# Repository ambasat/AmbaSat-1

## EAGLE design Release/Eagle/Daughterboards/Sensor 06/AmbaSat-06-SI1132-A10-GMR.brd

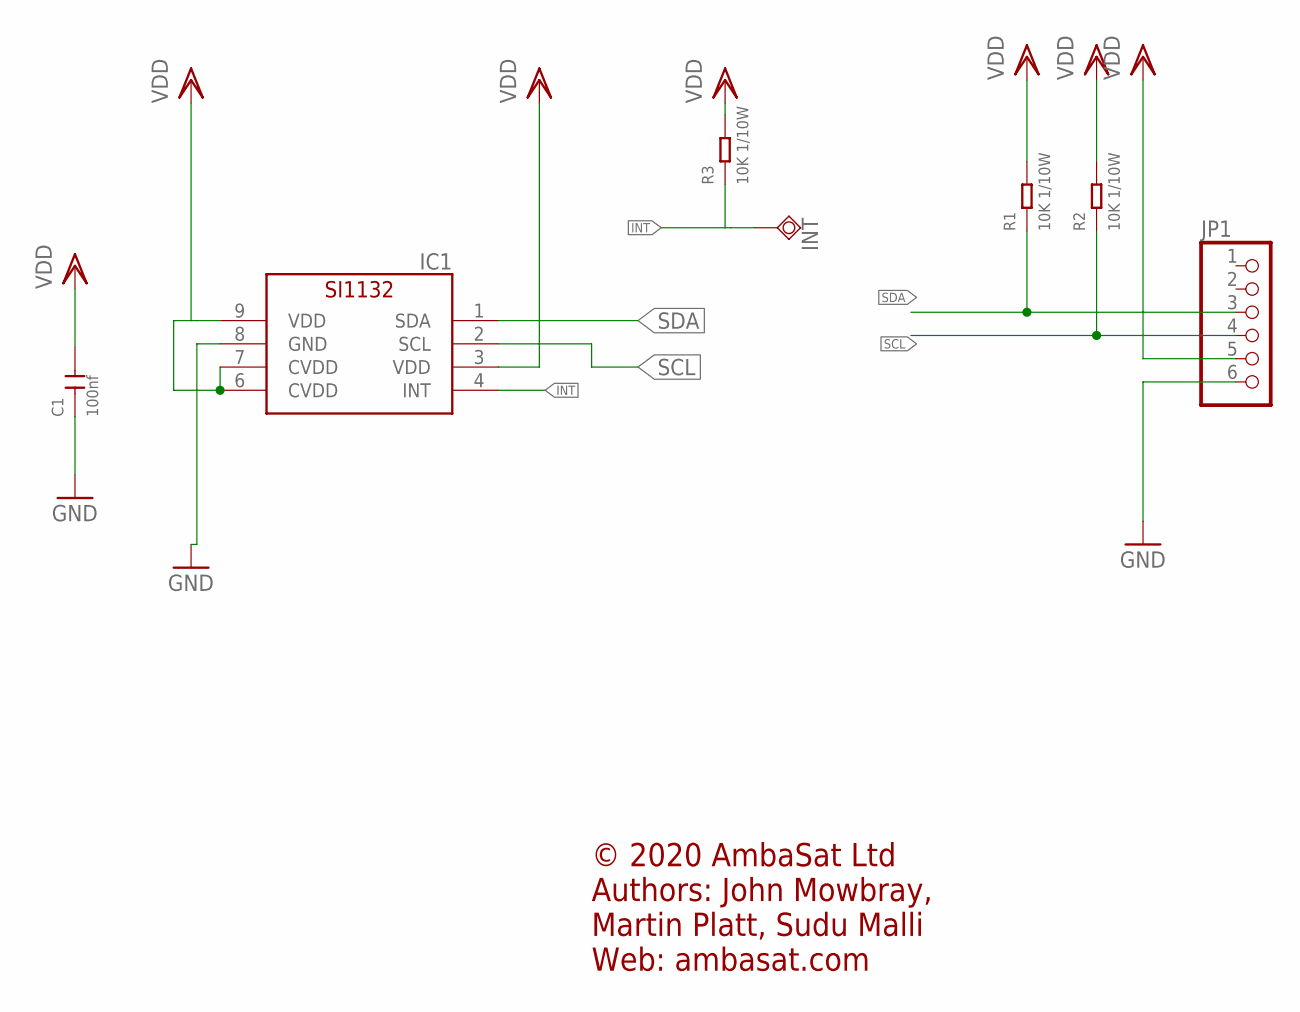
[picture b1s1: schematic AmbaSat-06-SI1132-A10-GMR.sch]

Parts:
C1: 100nf; C0603
IC1: SL-SI1132; SILICONLABS-SI1132
INT: TESTPAD_TPSQTP12R; TESTPAD_TP12R
JP1: HEADER-1X6; 1X06_OVAL
R1, R2, R3: 10K 1/10W; R0603

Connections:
GND: C1.1, IC1.8 (GND), JP1.6
INT: IC1.4 (INT), INT.TP, R3.1
SCL: IC1.2 (SCL), JP1.4, R2.1
SDA: IC1.1 (SDA), JP1.3, R1.1
VDD: C1.2, IC1.3 (VDD), IC1.6 (CVDD), IC1.7 (CVDD), IC1.9 (VDD), JP1.5, R1.2, R2.2, R3.2

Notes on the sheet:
© 2020 AmbaSat Ltd Authors: John Mowbray, Martin Platt, Sudu Malli Web: ambasat.com

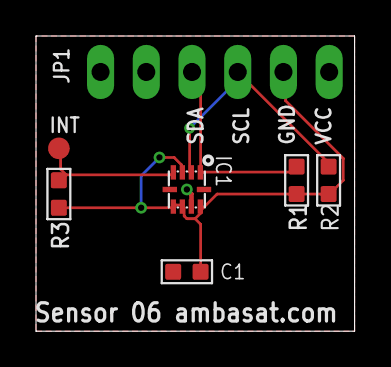
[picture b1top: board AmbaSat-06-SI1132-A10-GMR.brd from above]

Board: 2 copper layers, 17.7 x 16.4 mm, 7 parts (0 on the bottom side), 5 nets.

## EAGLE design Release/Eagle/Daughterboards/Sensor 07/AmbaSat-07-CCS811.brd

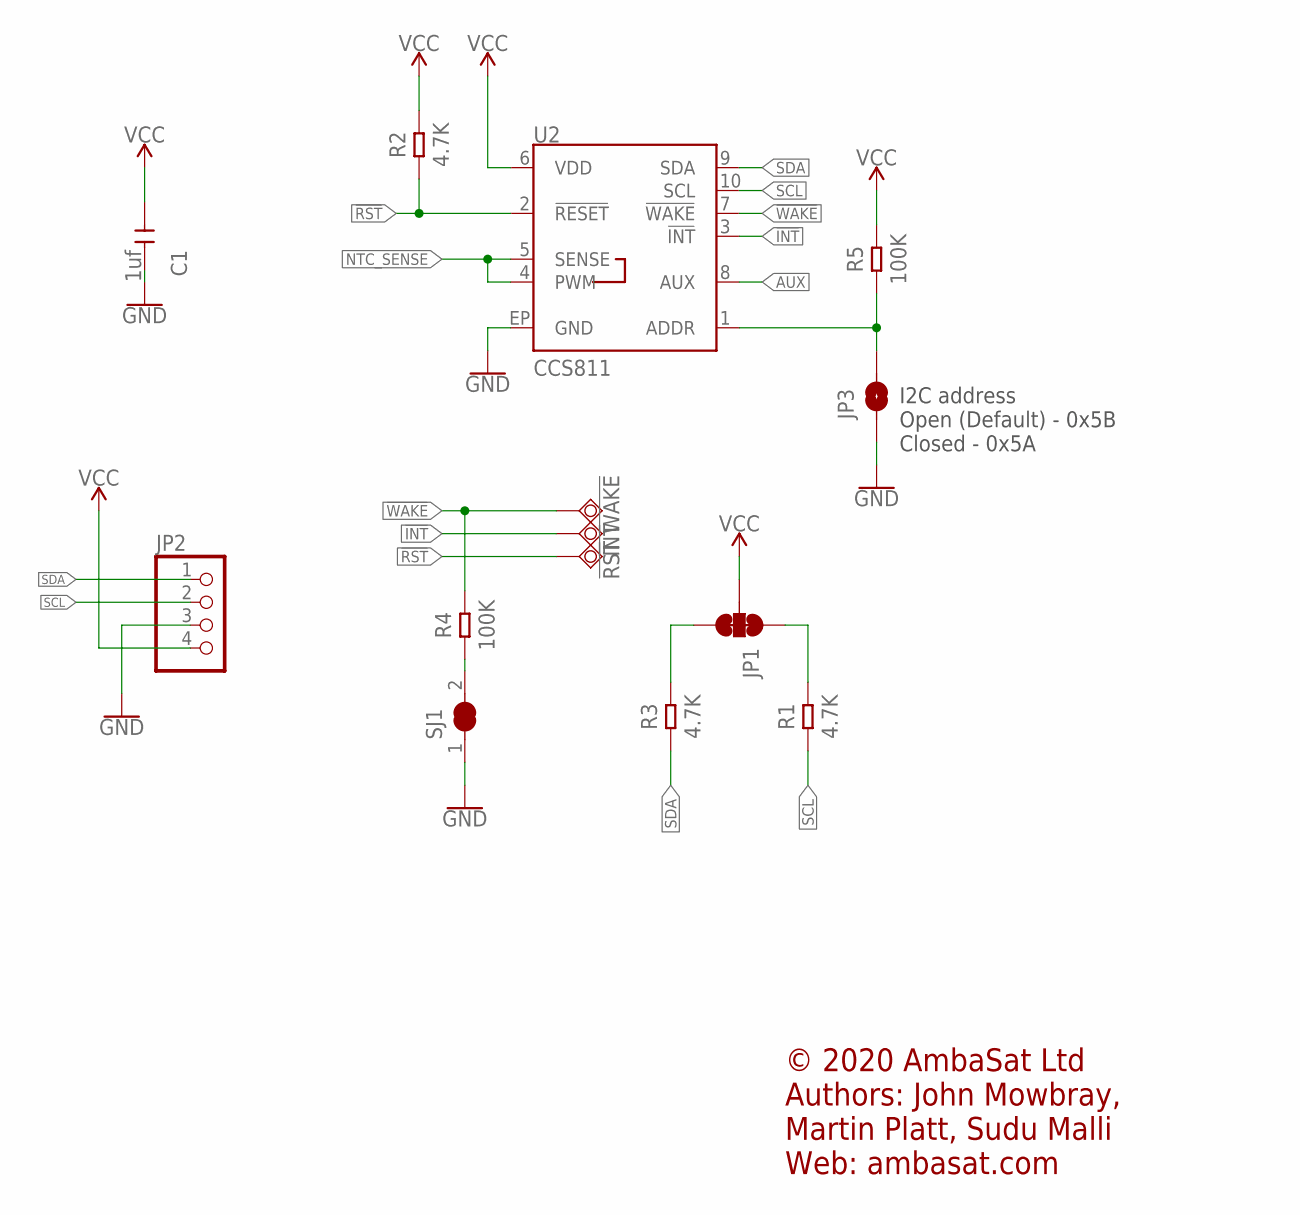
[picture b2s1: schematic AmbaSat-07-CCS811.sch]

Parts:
!INT: TESTPAD_TPSQTP14SQ; TESTPAD_TP14SQ
!RST: TESTPAD_TPSQTP14SQ; TESTPAD_TP14SQ
!WAKE: TESTPAD_TPSQTP14SQ; TESTPAD_TP14SQ
C1: 1uf; C0603
JP1: JUMPER-SMT_3_2-NC_TRACE_SILK; SMT-JUMPER_3_2-NC_TRACE_SILK
JP2: HEADER-1X4; 1X04_OVAL
JP3: JUMPER-SMT_2_NO_SILK; SMT-JUMPER_2_NO_SILK
R1, R2, R3: 4.7K; R0603
R4, R5: 100K; R0603
SJ1: SOLDERJUMPER_CLOSED; SOLDERJUMPER_CLOSEDWIRE
U2: CCS811; LGA10

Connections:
3.3V: C1.1, JP1.2, JP2.4, R2.2, R5.2, U2.6 (VDD)
!INT: !INT.TP, U2.3 (!INT!)
!RST: !RST.TP, R2.1, U2.2 (!RESET!)
!WAKE: !WAKE.TP, R4.2, U2.7 (!WAKE!)
AUX: U2.8 (AUX)
CCS811_ADDR: JP3.2, R5.1, U2.1 (ADDR)
GND: C1.2, JP2.3, JP3.1, SJ1.1, U2.EP (GND)
unnamed: R4.1, SJ1.2
unnamed: JP1.3, R3.2
unnamed: JP1.1, R1.2
NTC_SENSE: U2.4 (PWM), U2.5 (SENSE)
SCL: JP2.2, R1.1, U2.10 (SCL)
SDA: JP2.1, R3.1, U2.9 (SDA)

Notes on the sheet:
I2C address Open (Default) - 0x5B Closed - 0x5A
© 2020 AmbaSat Ltd Authors: John Mowbray, Martin Platt, Sudu Malli Web: ambasat.com

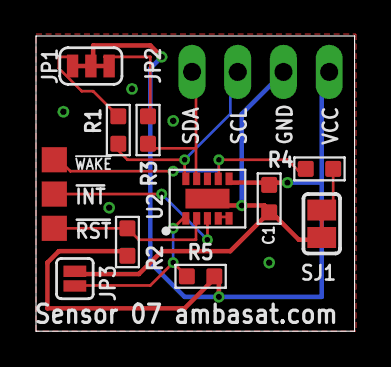
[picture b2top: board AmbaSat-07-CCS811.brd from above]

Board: 2 copper layers, 17.7 x 16.4 mm, 14 parts (0 on the bottom side), 12 nets.

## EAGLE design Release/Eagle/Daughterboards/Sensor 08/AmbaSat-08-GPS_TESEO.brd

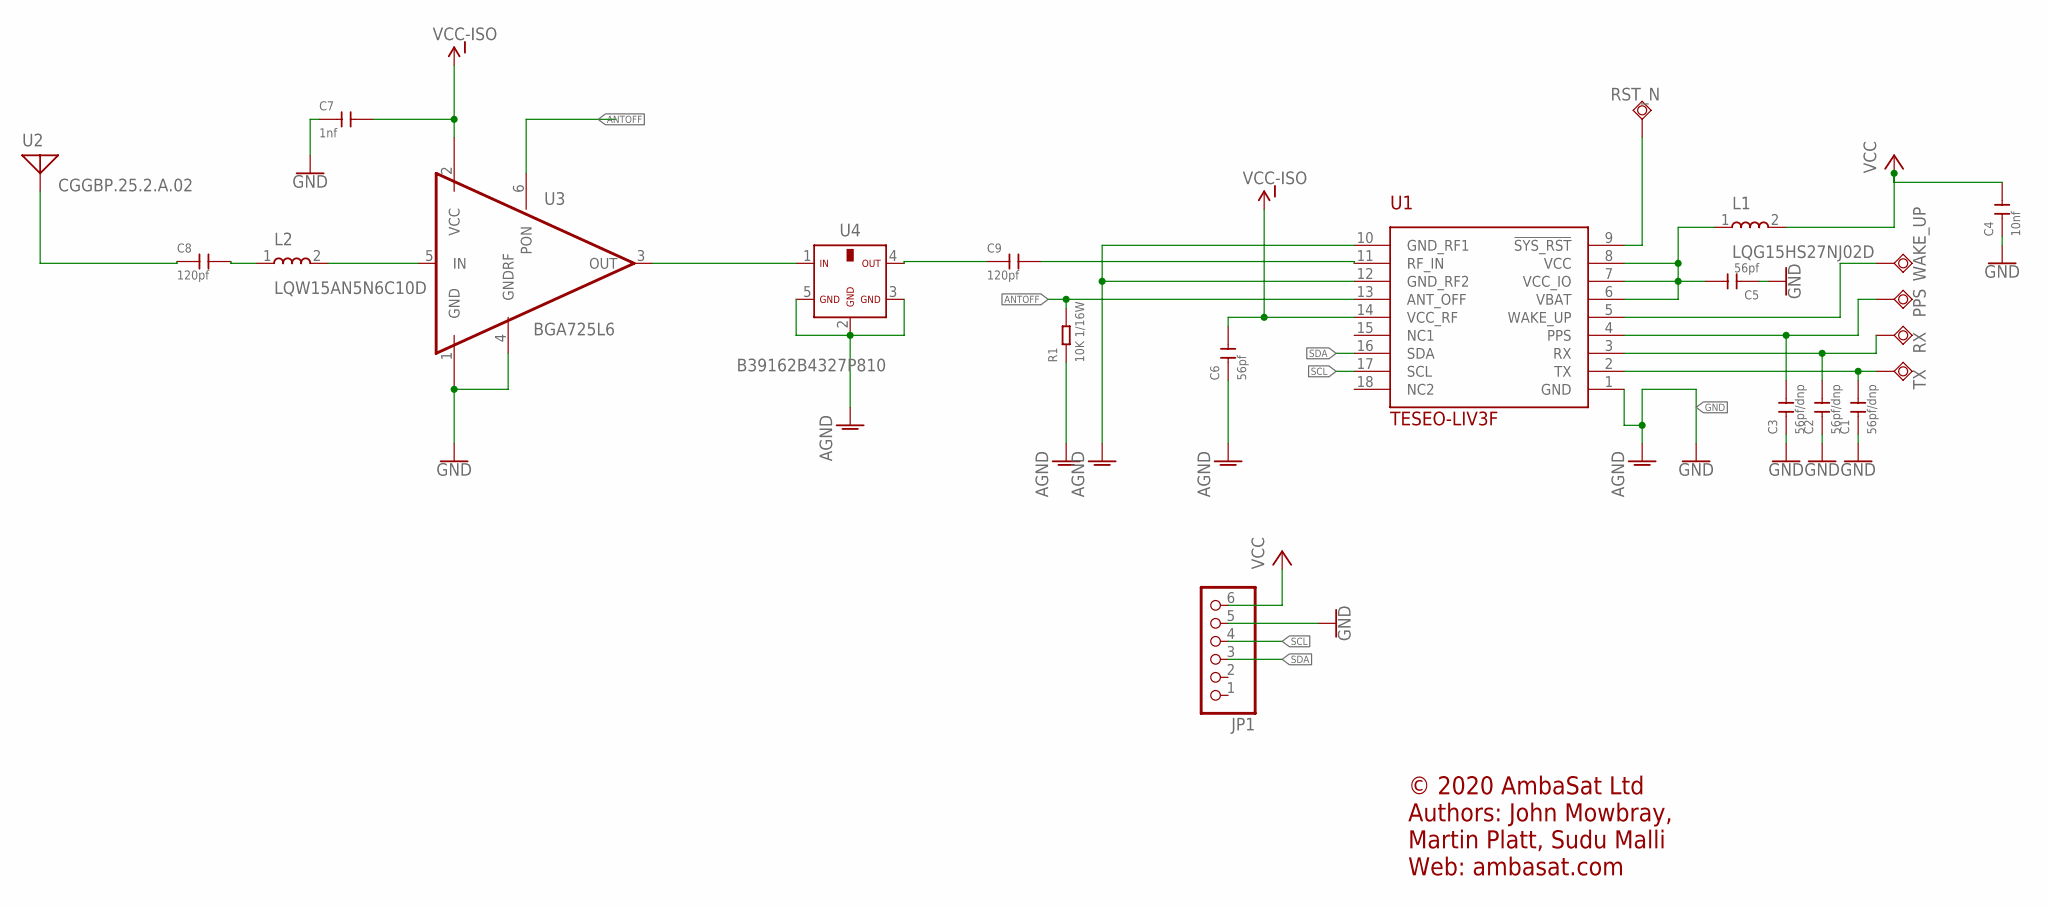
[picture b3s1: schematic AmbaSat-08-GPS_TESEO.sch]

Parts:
C1, C2, C3: 56pf/dnp; C0402; MPN CC0402JRNPO9BN560
C4: 10nf; C0402
C5, C6: 56pf; C0402; MPN CC0402JRNPO9BN560
C7: 1nf; C0402
C8, C9: 120pf; C0402; MPN CC0402JRNPO9BN121
JP1: HEADER-1X6; 1X06_OVAL
L1: LQG15HS27NJ02D; LQG15HN2N2S02D; MPN LQG15HS27NJ02D; DIGIKEY_PART_NUMBER 490-2628-1-ND
L2: LQW15AN5N6C10D; LQG15HN2N2S02D; MPN LQW15AN5N6C10D; DIGIKEY_PART_NUMBER 490-6833-1-ND
PPS: TESTPAD_TPSQTP11SQ; TESTPAD_TP11SQ
R1: 10K 1/16W; R0402
RST_N: TESTPAD_TPSQTP11SQ; TESTPAD_TP11SQ
RX: TESTPAD_TPSQTP11SQ; TESTPAD_TP11SQ
TX: TESTPAD_TPSQTP11SQ; TESTPAD_TP11SQ
U1: TESEO-LIV3F
U2: CGGBP.25.2.A.02; ANTENNA-PATCH
U3: BGA725L6; PSON35P100X100X35-6N
U4: B39162B4327P810; FIL_B39162B9417K610
WAKE_UP: TESTPAD_TPSQTP11SQ; TESTPAD_TP11SQ

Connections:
ANTOFF: R1.2, U1.13 (ANT_OFF), U3.6 (PON)
GND: C1.1, C2.1, C3.1, C4.1, C5.1, C6.1, C7.1, JP1.5, R1.1, U1.1 (GND), U1.10 (GND_RF1), U1.12 (GND_RF2), U3.1 (GND), U3.4 (GNDRF), U4.2 (GND3), U4.3 (GND2), U4.5 (GND)
unnamed: C1.2, TX.TP, U1.2 (TX)
unnamed: C2.2, RX.TP, U1.3 (RX)
unnamed: C3.2, PPS.TP, U1.4 (PPS)
unnamed: U1.5 (WAKE_UP), WAKE_UP.TP
unnamed: C5.2, L1.1, U1.6 (VBAT), U1.7 (VCC_IO), U1.8 (VCC)
unnamed: RST_N.TP, U1.9 (!SYS_RST)
unnamed: L2.2, U3.5 (IN)
unnamed: C8.2, L2.1
unnamed: C9.1, U4.4 (OUT)
unnamed: C9.2, U1.11 (RF_IN)
unnamed: C8.1, U2.ANT
unnamed: U3.3 (OUT), U4.1 (IN)
SCL: JP1.4, U1.17 (SCL)
SDA: JP1.3, U1.16 (SDA)
VCC: C4.2, JP1.6, L1.2
VCC-ISO: C6.2, C7.2, U1.14 (VCC_RF), U3.2 (VCC)

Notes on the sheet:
© 2020 AmbaSat Ltd Authors: John Mowbray, Martin Platt, Sudu Malli Web: ambasat.com

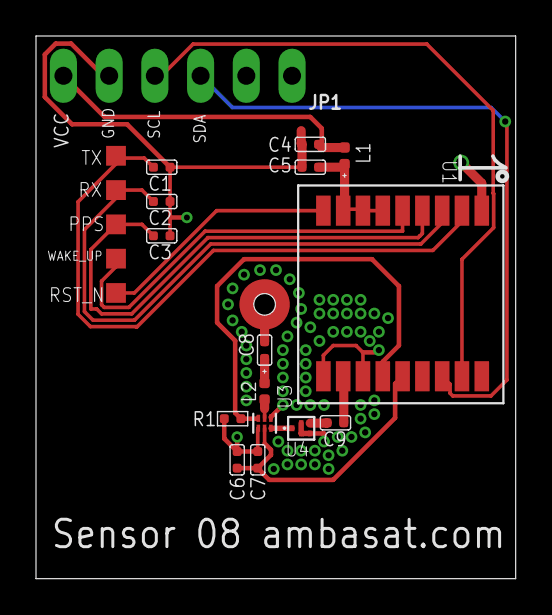
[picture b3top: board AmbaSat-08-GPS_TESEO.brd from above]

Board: 2 copper layers, 26.6 x 30.1 mm, 22 parts (0 on the bottom side), 18 nets.

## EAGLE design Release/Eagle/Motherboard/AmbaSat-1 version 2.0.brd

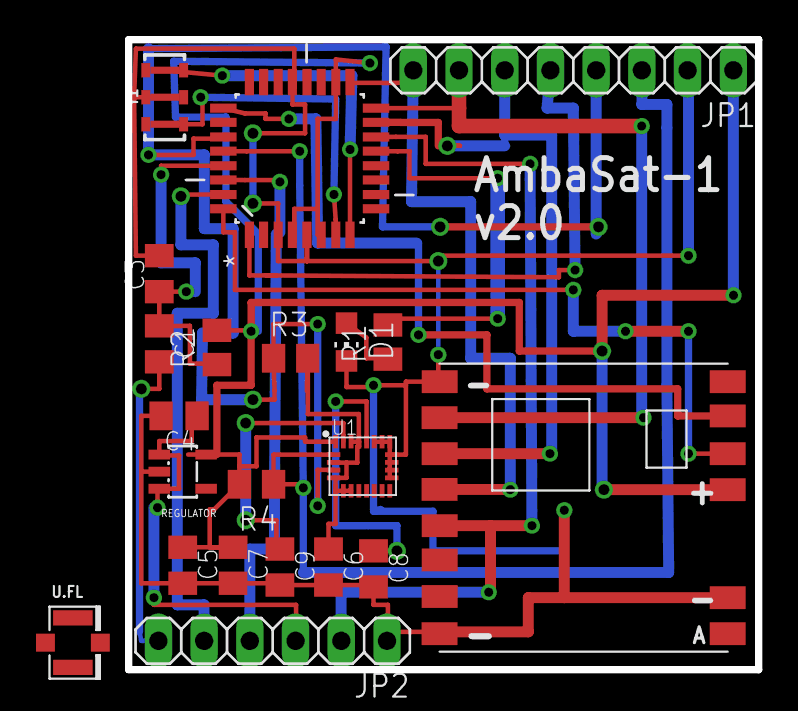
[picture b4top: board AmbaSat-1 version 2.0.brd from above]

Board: 2 copper layers, 35.0 x 35.0 mm, 21 parts (0 on the bottom side), 22 nets.

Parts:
ATMEGA328P-AU: ATMEGA328P-AU; QFP80P900X900X120-32N
C1, C4: 1uF; C0805K
C3, C7, C9: 0.1uF; C0805K
C5: 2.2uF; C0805K
C6: 10uF; C0805K
C8: 10nF; C0805K
D1: CHIP-LED0805
JP1: 1X08
JP2: 1X06
R1: 1k6; M0805
R2: 10k; M0805
R3, R4: 1K; M0805
REGULATOR: LP2985AIM5-3.3; SOT25
RFM95: RFM95
U1: LSM9DS1; LGA24-8X4
U.FL: U.FL
Y1: 4MHz; RESONATOR-SMD-4.5X2.0

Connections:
D3: ATMEGA328P-AU.1, JP1.5
DIO0: ATMEGA328P-AU.32, RFM95.DIO0
DIO1: ATMEGA328P-AU.25, RFM95.DIO1
GND: ATMEGA328P-AU.3, ATMEGA328P-AU.5, ATMEGA328P-AU.21, C3.2, C4.2, C5.2, C6.2, C7.2, C8.2, C9.2, D1.C, JP1.2, JP2.1, REGULATOR.2, RFM95.GND, RFM95.GND1, RFM95.GND2, U1.14, U1.15, U1.16, U1.17, U1.18, U1.19, U1.20, Y1.2
MISO: ATMEGA328P-AU.16, JP1.7, RFM95.MISO
MOSI: ATMEGA328P-AU.15, JP1.6, RFM95.MOSI
unnamed: ATMEGA328P-AU.7, Y1.1
unnamed: ATMEGA328P-AU.8, Y1.3
unnamed: ATMEGA328P-AU.13, R1.2
unnamed: D1.A, R1.1
unnamed: C1.2, JP2.6
unnamed: C9.1, U1.24
unnamed: C8.1, U1.21
RESET: ATMEGA328P-AU.29, C1.1, C3.1, R2.1
RX: ATMEGA328P-AU.30, JP2.4
SCK: ATMEGA328P-AU.17, JP1.8, RFM95.SCK
SCL: ATMEGA328P-AU.28, JP1.3, R4.1, U1.2
SDA: ATMEGA328P-AU.27, JP1.4, R3.1, U1.4
SS: ATMEGA328P-AU.14, JP2.2, RFM95.NSS
TX: ATMEGA328P-AU.31, JP2.5
VCC: ATMEGA328P-AU.4, ATMEGA328P-AU.6, ATMEGA328P-AU.18, C5.1, C6.1, C7.1, JP1.1, R2.2, R3.2, R4.2, REGULATOR.5, RFM95.VDD, U1.1, U1.3, U1.5, U1.6, U1.7, U1.8, U1.22, U1.23
VIN: C4.1, JP2.3, REGULATOR.1, REGULATOR.3

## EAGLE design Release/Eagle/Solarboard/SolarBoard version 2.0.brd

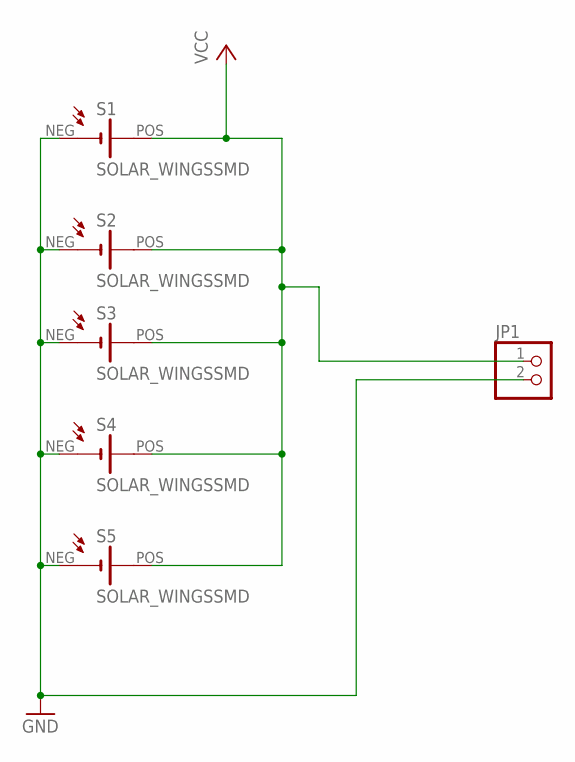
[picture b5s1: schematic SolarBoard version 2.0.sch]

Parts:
JP1: PINHD-1X2; 1X02
S1, S2, S3, S4, S5: SOLAR_WINGSSMD; SOLAR_WINGS_SMD

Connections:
GND: JP1.2, S1.NEG, S2.NEG, S3.NEG, S4.NEG, S5.NEG
VCC: JP1.1, S1.POS, S2.POS, S3.POS, S4.POS, S5.POS

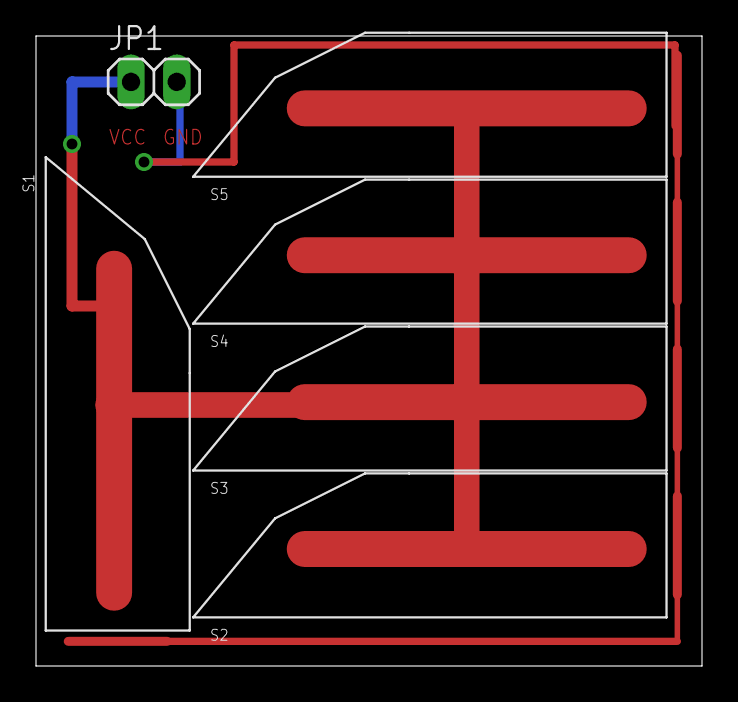
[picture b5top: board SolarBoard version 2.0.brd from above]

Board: 2 copper layers, 37.0 x 35.0 mm, 6 parts (0 on the bottom side), 2 nets.

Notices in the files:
parts and their libraries:
microbuilder: This work is placed in the public domain, and may be freely used for commercial and non-commercial work with the following conditions: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
FaBo-Mems: Released under the Creative Commons Attribution-ShareAlike 4.0 License
https://creativecommons.org/licenses/by-sa/4.0
